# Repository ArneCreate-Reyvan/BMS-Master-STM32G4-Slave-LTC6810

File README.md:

# Master-Slave Battery Management System
### STM32G4 Master Controller · LTC6810 Slave Monitoring

A distributed Battery Management System (BMS) designed for a **102S2P electric vehicle battery pack**, featuring an STM32G4-based master controller and LTC6810-based slave monitoring units.

The system implements a modular master-slave architecture with **isoSPI daisy-chain communication**, enabling distributed battery cell voltage monitoring, temperature monitoring, centralized fault detection, and telemetry.

---

## Table of Contents

- [Overview](#overview)
- [Battery Pack Configuration](#battery-pack-configuration)
- [System Architecture](#system-architecture)
- [Monitoring Capabilities](#monitoring-capabilities)
- [Hardware Design](#hardware-design)
  - [Master BMS](#1-master-bms--stm32g4)
  - [Slave BMS](#2-slave-bms--ltc6810)
- [Communication Architecture](#communication-architecture)
- [Repository Structure](#repository-structure)
- [Development Tools](#development-tools)
- [Project Status](#project-status)
- [Future Improvements](#future-improvements)
- [Disclaimer](#disclaimer)

---

## Overview

The Battery Management System is responsible for monitoring and managing battery operating conditions to support safe and reliable electric vehicle operation.

This project implements a distributed monitoring architecture consisting of two primary subsystems:

- **Master BMS:** An STM32G4-based controller responsible for centralized system supervision, data acquisition, fault detection, and telemetry management.
- **Slave BMS:** LTC6810-based monitoring units responsible for individual battery module voltage and temperature monitoring.

The architecture separates module-level battery monitoring from high-level system management, allowing the battery pack to be monitored through interconnected slave units coordinated by a central master controller.

The hardware and PCB designs were developed using KiCad, with dedicated circuits for master control, battery monitoring, and inter-board communication.

## Battery Pack Configuration

The BMS is designed to support a **102S2P battery pack**, organized into 17 battery modules connected in series.

Each module consists of 6 series-connected cell groups, with each group containing 2 cells connected in parallel (6S2P per module).

This configuration results in 102 series-connected cell groups across the complete battery pack.

| Parameter | Specification |
|---|---|
| Battery Configuration | 102S2P |
| Total Battery Modules | 17 |
| Configuration per Module | 6S2P |
| Series Voltage Taps per Module | 6 |
| Temperature Sensors per Module | Up to 4 NTC thermistors |
| Total Voltage Monitoring Points | 102 |
| Maximum Temperature Monitoring Points | 68 |

### Battery Monitoring Distribution

Each module is equipped with local monitoring capabilities:

| Monitoring Parameter | Per Module | Entire Battery Pack |
|---|---:|---:|
| Cell Group Voltage | 6 channels | 102 channels |
| NTC Temperature | Up to 4 channels | Up to 68 channels |

This modular configuration enables the system to collect battery operating data across all 17 modules while maintaining centralized supervision.

### Main Subsystems

| Subsystem | Main Component | Responsibility |
|---|---|---|
| Master Controller | STM32G4 | Centralized control and system supervision |
| Slave Monitoring | LTC6810 | Battery cell voltage and temperature monitoring |
| Inter-board Communication | isoSPI | Isolated serial communication through a daisy-chain topology |
| Temperature Sensing | NTC Thermistors | Battery module temperature measurement |
| Data Management | STM32G4 | Monitoring data processing and telemetry |
| Fault Management | STM32G4 | Centralized fault detection and system response |

## Monitoring Capabilities

### 1. Cell Voltage Monitoring

Each slave monitoring unit uses the LTC6810 battery monitoring IC to measure six series-connected cell-group voltages within its respective battery module.

Features:
- Individual cell-group voltage measurement.
- Monitoring of all 102 series-connected cell groups.
- Distributed voltage acquisition across 17 battery modules.
- Centralized monitoring data collection.

### 2. Temperature Monitoring

Each battery module supports up to four NTC thermistors for temperature measurement.

Features:
- Up to four temperature sensing channels per module.
- Maximum of 68 temperature monitoring points across the battery pack.
- Temperature data acquisition through the slave monitoring units.
- Centralized temperature monitoring and fault evaluation.

### 3. Fault Detection

The master controller processes monitoring data received from the slave units to evaluate battery operating conditions.

The architecture supports centralized evaluation of voltage and temperature measurements to identify abnormal battery conditions.

### 4. Telemetry

The master controller manages battery monitoring data and provides a centralized interface for system-level telemetry.

Monitoring information can be collected and processed for external system integration and battery status visualization.

## Hardware Design

The hardware consists of two primary PCB designs: the Master BMS and Slave BMS.

All schematics and PCB layouts were developed using KiCad.

---

### 1. Master BMS | STM32G4

<summary>Master BMS hardware overview</summary>

**Main Controller:** STM32G4

**Primary Responsibilities:**
- Centralized BMS control and supervision.
- Communication with LTC6810 slave monitoring units.
- Monitoring data acquisition and processing.
- Battery voltage and temperature data management.
- Fault detection and system-level monitoring.
- Telemetry management.

#### Schematic

#### PCB Layout

#### PCB 3D View

---

### 2. Slave BMS | LTC6810

<summary>Slave BMS hardware overview</summary>

**Battery Monitoring IC:** LTC6810

**Primary Responsibilities:**
- Monitoring six series-connected cell-group voltages per module.
- Acquiring temperature measurements from up to four NTC thermistors per module.
- Communicating monitoring data through the isoSPI interface.
- Supporting distributed battery monitoring across 17 modules.

#### Schematic

#### PCB Layout

#### PCB 3D View

---

## Communication Architecture

The system uses **isoSPI communication** to establish communication between the STM32G4 master controller and the LTC6810 slave monitoring ICs.

The LTC6810 devices are interconnected through an **isoSPI daisy-chain topology**, allowing monitoring data to be transferred across multiple slave units through a serial communication chain.

### Communication Structure

- **Master Interface:** STM32G4 communicates with the first LTC6810 through an SPI-to-isoSPI interface.
- **Slave Communication:** LTC6810 devices communicate through their isoSPI interfaces.
- **Topology:** Daisy-chain configuration connecting the monitoring ICs.
- **Data Acquisition:** The master controller coordinates communication and collects battery monitoring information from the slave units.

### Communication Advantages

- Differential communication over twisted-pair connections.
- Galvanically isolated communication between battery monitoring circuits and the master interface when implemented with the appropriate isolation coupling components.
- Reduced wiring complexity compared with individual communication connections to every monitoring unit.
- Scalable communication architecture for distributed battery monitoring.

## Development Tools

| Tool / Component | Purpose |
|---|---|
| KiCad | Schematic capture and PCB design |
| STM32G4 | Master microcontroller |
| LTC6810 | Battery cell monitoring IC |
| isoSPI | Isolated serial communication interface |
| NTC Thermistors | Temperature sensing |
| Embedded C/C++ | Firmware development |

## Project Status

The hardware and firmware development have been completed, with further refinement and validation remaining.

| Development Area | Status |
|---|---|
| System Architecture | Completed |
| Master BMS Hardware | Completed |
| Slave BMS Hardware | Completed |
| PCB Design | Completed |
| Master Firmware | Developed |
| Slave Firmware | Developed |
| Communication Implementation | Developed |
| Documentation | Ongoing |
| Design Refinement & Validation | Ongoing |

## Future Improvements

- Further refinement of schematic and PCB designs.
- Additional communication reliability testing.
- Expanded battery fault detection and protection mechanisms.
- Improved telemetry and monitoring capabilities.
- Further validation of voltage and temperature measurement accuracy.
- System-level integration and testing.

## Disclaimer

This project is an engineering development project intended for educational and electric vehicle research purposes.

The documented design should not be considered a production-ready battery protection system without appropriate electrical, functional, and safety validation.

High-voltage battery systems require proper insulation, isolation, protection mechanisms, and qualified engineering supervision before physical implementation.

---

**Developed for electric vehicle battery management and high-voltage electrical system applications.**

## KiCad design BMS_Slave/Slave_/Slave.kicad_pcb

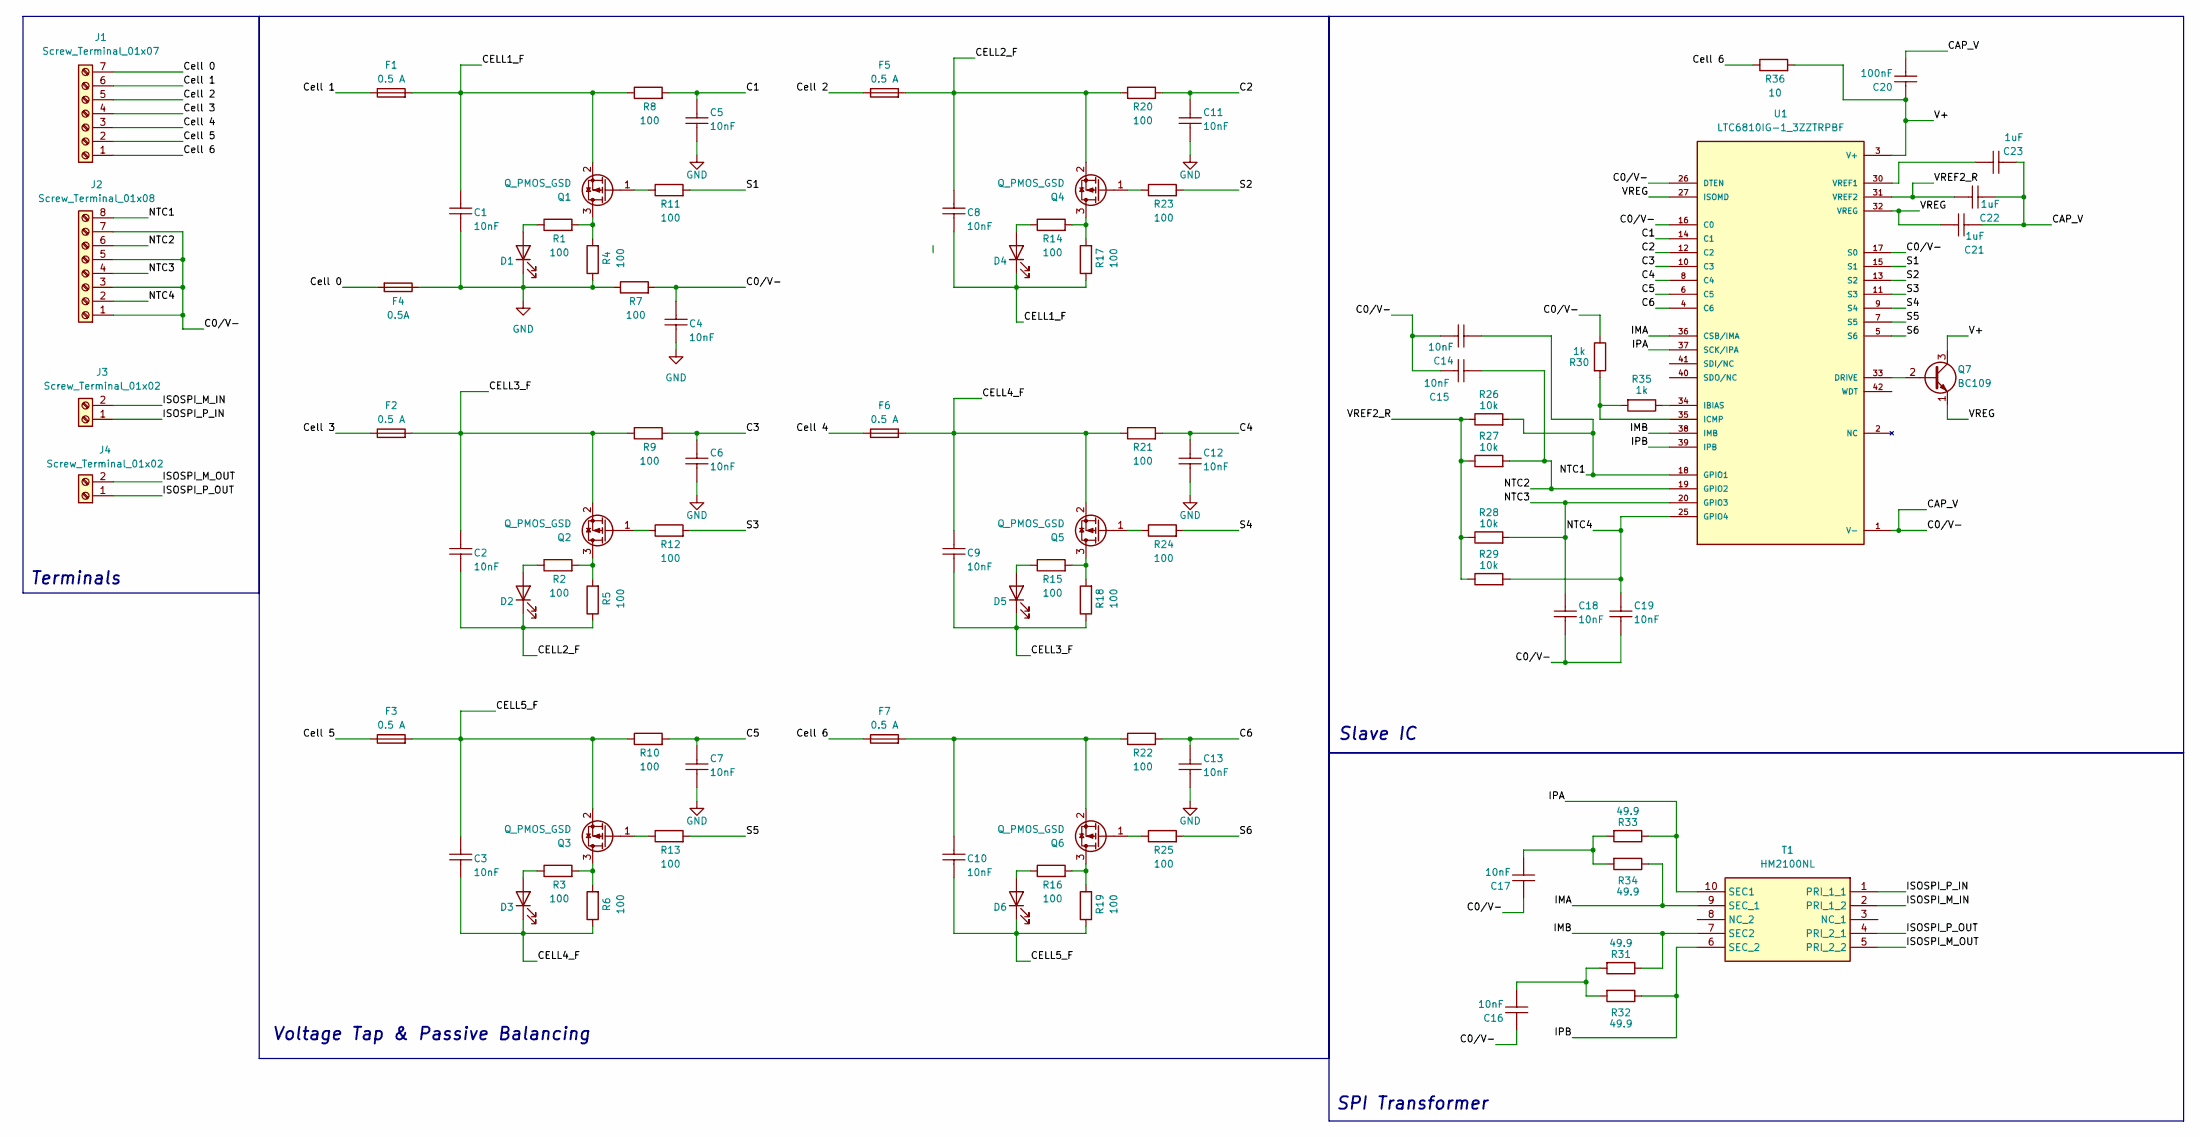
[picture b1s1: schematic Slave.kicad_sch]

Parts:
C1, C2, C3, C4, C5, C6, C7, C8, C9, C10, C11, C12, C13, C14, C15, C16, C17, C18, C19: 10nF; C_0603_1608Metric
C20: 100nF; C_0603_1608Metric
C21, C22, C23: 1uF; C_0603_1608Metric
D1, D2, D3, D4, D5, D6: LED; LED_0603_1608Metric
F1, F2, F3, F5, F6, F7: 0.5 A; Fuse_1206_3216Metric
F4: 0.5A; Fuse_1206_3216Metric
J1: Screw_Terminal_01x07; TerminalBlock_Phoenix_MKDS-1,5-7-5.08_1x07_P5.08mm_Horizont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
J2: Screw_Terminal_01x08; TerminalBlock_Phoenix_MKDS-1,5-8-5.08_1x08_P5.08mm_Horizont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
J3, J4: Screw_Terminal_01x02; TerminalBlock_Phoenix_MKDS-1,5-2-5.08_1x02_P5.08mm_Horizont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
Q1, Q2, Q3, Q4, Q5, Q6: Q_PMOS_GSD; SOT-23
Q7: BC109; TO-18-3
R1, R2, R3, R4, R5, R6, R7, R8, R9, R10, R11, R12, R13, R14, R15, R16, R17, R18, R19, R20, R21, R22, R23, R24, R25: 100; R_0805_2012Metric
R26, R27, R28, R29: 10k; R_0201_0603Metric
R30, R35: 1k; R_0201_0603Metric
R31, R32, R33, R34: 49.9; R_0201_0603Metric
R36: 10; R_0201_0603Metric
T1: HM2100NL; SOP254P1493X345-10N; Mouser Part Number 673-HM2100NL
U1: LTC6810IG-1_3ZZTRPBF; 05-08-1754_ADI-L; MPN LTC6810IG-1#3ZZTRPBF

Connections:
/C1: C5.1, R8.2, U1.14 (C1)
/C2: C11.1, R20.2, U1.12 (C2)
/C3: C6.1, R9.2, U1.10 (C3)
/C4: C12.1, R21.2, U1.8 (C4)
/C5: C7.1, R10.2, U1.6 (C5)
/C6: C13.1, R22.2, U1.4 (C6)
/CELL1_F: C1.1, C8.2, D4.1 (K), F1.2, Q1.2 (S), R8.1, R17.1
/CELL2_F: C2.2, C8.1, D2.1 (K), F5.2, Q4.2 (S), R5.1, R20.1
/CELL3_F: C2.1, C9.2, D5.1 (K), F2.2, Q2.2 (S), R9.1, R18.1
/CELL4_F: C3.2, C9.1, D3.1 (K), F6.2, Q5.2 (S), R6.1, R21.1
/CELL5_F: C3.1, C10.2, D6.1 (K), F3.2, Q3.2 (S), R10.1, R19.1
/Cell 0: F4.2, J1.7
/Cell 1: F1.1, J1.6
/Cell 2: F5.1, J1.5
/Cell 3: F2.1, J1.4
/Cell 4: F6.1, J1.3
/Cell 5: F3.1, J1.2
/Cell 6: F7.1, J1.1, R36.1
/IMA: R34.1, T1.9 (SEC_1), U1.36 (CSB/IMA)
/IMB: R31.1, T1.7 (SEC2), U1.38 (IMB)
/IPA: R33.1, T1.10 (SEC1), U1.37 (SCK/IPA)
/IPB: R32.1, T1.6 (SEC_2), U1.39 (IPB)
/ISOSPI_M_IN: J3.2, T1.2 (PRI_1_2)
/ISOSPI_M_OUT: J4.2, T1.5 (PRI_2_2)
/ISOSPI_P_IN: J3.1, T1.1 (PRI_1_1)
/ISOSPI_P_OUT: J4.1, T1.4 (PRI_2_1)
/NTC1: C14.1, J2.8, R26.2, U1.18 (GPIO1)
/NTC2: C15.1, J2.6, R27.2, U1.19 (GPIO2)
/NTC3: C18.1, J2.4, R28.2, U1.20 (GPIO3)
/NTC4: C19.1, J2.2, R29.2, U1.25 (GPIO4)
/S1: R11.2, U1.15 (S1)
/S2: R23.2, U1.13 (S2)
/S3: R12.2, U1.11 (S3)
/S4: R24.2, U1.9 (S4)
/S5: R13.2, U1.7 (S5)
/S6: R25.2, U1.5 (S6)
/V+: C20.1, Q7.3 (C), R36.2, U1.3 (V+)
/VREF2_R: C22.1, R26.1, R27.1, R28.1, R29.1, U1.31 (VREF2)
/VREG: C21.1, Q7.1 (E), U1.27 (ISOMD), U1.32 (VREG)
GND: C1.2, C4.2, C5.2, C6.2, C7.2, C11.2, C12.2, C13.2, D1.1 (K), F4.1, R4.1, R7.1
unnamed: C16.2, R31.2, R32.2
unnamed: C17.2, R33.2, R34.2
unnamed: D1.2 (A), R1.1
unnamed: D2.2 (A), R2.1
unnamed: D3.2 (A), R3.1
unnamed: D4.2 (A), R14.1
unnamed: D5.2 (A), R15.1
unnamed: D6.2 (A), R16.1
unnamed: Q1.3 (D), R1.2, R4.2
unnamed: Q1.1 (G), R11.1
unnamed: Q2.3 (D), R2.2, R5.2
unnamed: Q2.1 (G), R12.1
unnamed: Q3.3 (D), R3.2, R6.2
unnamed: Q3.1 (G), R13.1
unnamed: Q4.3 (D), R14.2, R17.2
unnamed: Q4.1 (G), R23.1
unnamed: Q5.3 (D), R15.2, R18.2
unnamed: Q5.1 (G), R24.1
unnamed: Q6.3 (D), R16.2, R19.2
unnamed: Q6.1 (G), R25.1
unnamed: C10.1, F7.2, Q6.2 (S), R22.1
unnamed: Q7.2 (B), U1.33 (DRIVE)
unnamed: R35.1, U1.34 (IBIAS)
unnamed: R30.2, R35.2, U1.35 (ICMP)
unnamed: C23.1, U1.30 (VREF1)
V-: C4.1, C14.2, C15.2, C16.1, C17.1, C18.2, C19.2, C20.2, C21.2, C22.2, C23.2, J2.1, J2.3, J2.5, J2.7, R7.2, R30.1, U1.1 (V-), U1.16 (C0), U1.17 (S0), U1.21 (V-), U1.22 (V-), U1.23 (V-), U1.24 (V-), U1.26 (DTEN), U1.28 (V-), U1.29 (V-), U1.43 (V-), U1.44 (V-)

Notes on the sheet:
SPI Transformer
Terminals
Slave IC
Voltage Tap & Passive Balancing

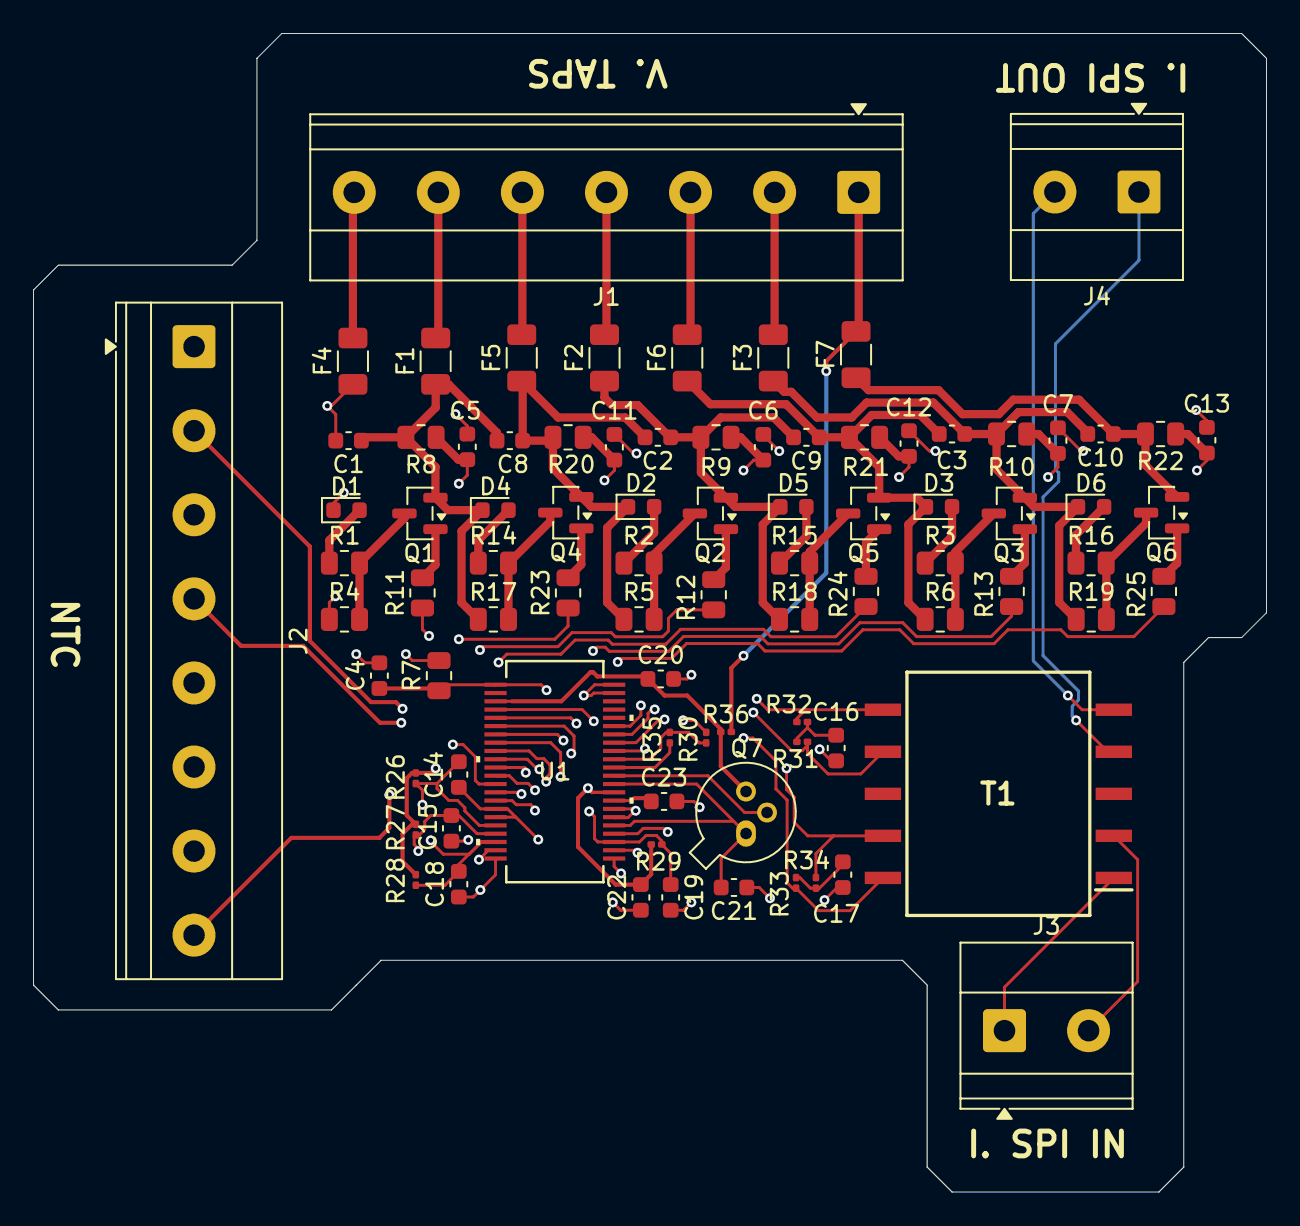
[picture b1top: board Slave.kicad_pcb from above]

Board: 4 copper layers, 74.5 x 70.0 mm, 85 parts (0 on the bottom side), 66 nets.

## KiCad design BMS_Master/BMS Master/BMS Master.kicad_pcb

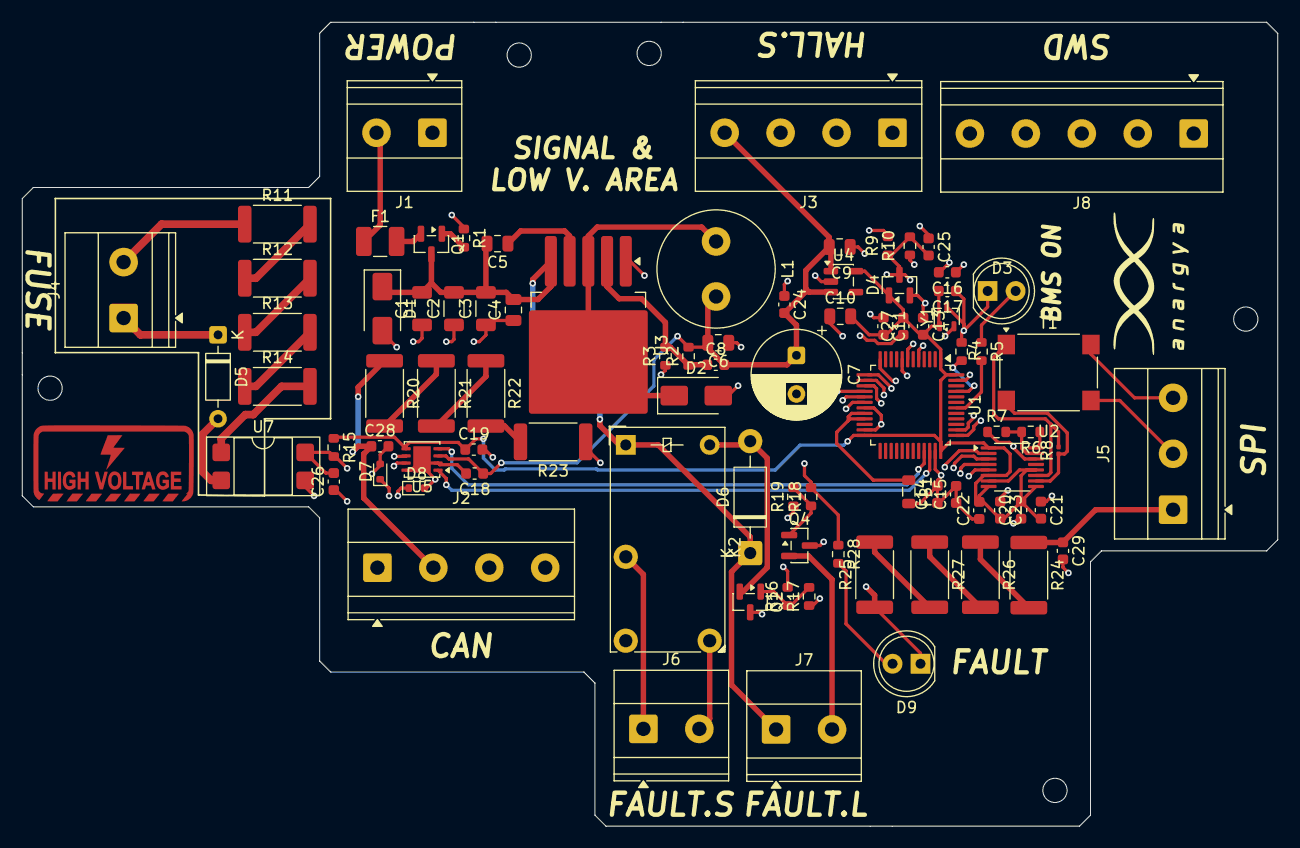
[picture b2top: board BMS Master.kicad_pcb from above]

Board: 4 copper layers, 114.0 x 73.0 mm, 88 parts (0 on the bottom side), 59 nets.

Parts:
C1, C2: 10uF; C_1206_3216Metric
C3: 220uF; C_1206_3216Metric
C4, C5, C6: 1uF; C_0805_2012Metric
C7: 330uF; CP_Radial_D8.0mm_P3.50mm
C8: 33nF; C_0603_1608Metric
C9, C10: 10uF; C_0805_2012Metric
C11, C13, C15, C16, C17, C18, C19, C20, C22, C24, C25, C26, C27, C28, C29: 100nF; C_0603_1608Metric
C14, C21, C23: 1uF; C_0603_1608Metric
D1: SMAJ24A; D_SMA
D2: D_Schottky; D_SMA
D3, D9: LED; LED_D5.0mm
D4: BAT54S; SOT-23
D5: 1N4148; D_DO-35_SOD27_P7.62mm_Horizontal
D6: 1N4007; D_DO-41_SOD81_P10.16mm_Horizontal
D7, D8: ESD5Zxx; D_SOD-523
F1: Fuse; Fuse_1210_3225Metric_Pad1.42x2.65mm_HandSolder
FB1: FerriteBead; L_0805_2012Metric
J1, J4, J6, J7: Screw_Terminal_01x02; TerminalBlock_Phoenix_MKDS-1,5-2-5.08_1x02_P5.08mm_Horizont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
J2, J3: Screw_Terminal_01x04; TerminalBlock_Phoenix_MKDS-1,5-4-5.08_1x04_P5.08mm_Horizont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
J5: Screw_Terminal_01x03; TerminalBlock_Phoenix_MKDS-1,5-3-5.08_1x03_P5.08mm_Horizont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
J8: Screw_Terminal_01x05; TerminalBlock_Phoenix_MKDS-1,5-5-5.08_1x05_P5.08mm_Horizont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
K2: FINDER-32.21-x000; Relay_SPDT_Finder_32.21-x000
L1: 47uH; L_Radial_D10.5mm_P5.00mm_Abacron_AISR-01
Q1: NTR2101P; SOT-23
Q2, Q4: 2N7002; SOT-23
R1, R2, R3, R4, R9, R10, R15: 10k; R_0603_1608Metric
R5, R16, R18, R28: 1k; R_0603_1608Metric
R6: 1.21k; R_0603_1608Metric
R7: 787; R_0603_1608Metric
R8: 100; R_0201_0603Metric
R11, R12, R13, R14: 75k; R_2512_6332Metric
R17, R19: 100k; R_0603_1608Metric
R20, R21, R22, R23, R24, R25, R26, R27: 250k; R_2512_6332Metric
T1: PE-68386NL; Pulse_PA2001NL
U1: STM32G473CBTx; LQFP-48_7x7mm_P0.5mm
U2: LTC6820; MSOP-16_3x4.039mm_P0.5mm
U3: XL4015; TO-263-5_TabPin3
U4: AP2112K-3.3; SOT-23-5
U5: TJA1051TK-3; HVSON-8-1EP_3x3mm_P0.65mm_EP1.6x2.4mm
U7: Optocoupler_DC_PhotoNPN_AKEC; DIP-4_W7.62mm_SMDSocket_SmallPads
Y1: MAX7375AXR805; SOT-323_SC-70

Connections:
/12V_LV: F1.1, J1.2
/12V_SW: C1.2, C2.2, C3.2, C4.2, C5.2, D1.1 (A1), D6.1 (K), J7.1, K2.A1, Q1.3 (D), U3.5 (VIN)
/+5V: C6.2, C7.1, C8.2, C9.2, C18.1, C24.2, J3.4, L1.2, R2.2, U4.1 (VIN), U4.3 (EN), U5.3 (VCC)
/CAN_H: D8.1 (K), J2.4, U5.7 (CANH)
/CAN_L: D7.1 (K), J2.3, U5.6 (CANL)
/COM: J6.2, K2.12
/FAULT_LED: R18.2, R28.1, U1.18 (PB2)
/FAULT_SIG: R16.2, U1.17 (PB1)
/FUSE_A: J4.2, R11.1
/FUSE_B: D5.1 (K), J4.1
/GPIO_12: U1.12 (PA4), U2.5 (CS#)
/HALL_OUT: J3.3, R9.2
/HALL_VOLT: C25.2, D4.3 (COM), R9.1, R10.2, U1.8 (PA0)
/ISOSPI_M: J5.2, T1.4
/ISOSPI_P: J5.3, T1.6
/LAMP_SINK: J7.2, Q4.2 (S)
/LDO_OUT_3V3: C10.2, C11.2, C13.2, C17.2, C19.1, C20.2, C21.2, C22.2, C23.2, C27.2, D4.1 (A), R15.1, U1.1 (VBAT), U1.24 (VDD), U1.36 (VDD), U1.48 (VDD), U2.1 (EN), U2.6 (VDDS), U2.7 (POL), U2.8 (PHA), U2.9 (VDD), U2.12 (MSTR), U4.5 (VOUT), U5.5 (VIO), Y1.1 (V+)
/NO: J6.1, K2.11
/NRST: C16.2, J8.4, U1.7 (PG10)
/OPTO_COL: C26.2, R15.2, U1.16 (PB0), U7.4
/PRIM_1: R8.2, T1.1, U2.11 (IP)
/PRIM_2: R8.1, T1.3, U2.10 (IM)
/RXD: U1.33 (PA11), U5.4 (RXD)
/SHIELD_CAN: C28.1, J2.2, R20.1
/SHIELD_SPI: C29.1, J5.1, R24.1
/SPI1_MISO: U1.14 (PA6), U2.3 (MISO)
/SPI1_MOSI: U1.15 (PA7), U2.2 (MOSI)
/SPI1_SCK: U1.13 (PA5), U2.4 (SCK)
/SWCLK: J8.3, U1.38 (PA14)
/SWDIO: J8.2, U1.37 (PA13)
/TXD: U1.34 (PA12), U5.1 (TXD)
/VDDA: FB1.1, U1.20 (VREF+), U1.21 (VDDA)
GND: C1.1, C2.1, C3.1, C4.1, C6.1, C7.2, C9.1, C10.1, C11.1, C13.1, C14.1, C14.2, C15.1, C15.2, C16.1, C17.1, C18.2, C19.2, C20.1, C21.1, C22.1, C23.1, C24.1, C25.1, C26.1, C27.1, C28.2, C29.2, D1.2 (A2), D2.2 (A), D3.1 (K), D4.2 (K), D7.2 (A), D8.2 (A), D9.1 (K), FB1.2, J1.1, J2.1, J3.1, J8.1, Q2.3 (D), Q4.3 (D), R1.1, R3.1, R4.1, R7.1, R10.1, R17.1, R19.1, R23.1, R25.1, U1.19 (VSSA), U1.23 (VSS), U1.35 (VSS), U1.47 (VSS), U2.14 (GND), U3.1 (GND), U4.2 (GND), U5.2 (GND), U5.8 (S), U5.9 (GND), U7.3, Y1.3 (GND)
unnamed: D2.1 (K), L1.1, U3.3 (SW)
unnamed: D3.2 (A), R5.1
unnamed: D5.2 (A), U7.2
unnamed: D6.2 (A), K2.A2, Q2.2 (S)
unnamed: D9.2 (A), R28.2
unnamed: Q1.1 (G), R1.2
unnamed: F1.2, Q1.2 (S)
unnamed: Q2.1 (G), R16.1, R17.2
unnamed: Q4.1 (G), R18.1, R19.2
unnamed: R11.2, R12.1
unnamed: R12.2, R13.1
unnamed: R13.2, R14.1
unnamed: R14.2, U7.1
unnamed: R20.2, R21.1
unnamed: R21.2, R22.1
unnamed: R22.2, R23.2
unnamed: R24.2, R26.1
unnamed: R25.2, R27.2
unnamed: R26.2, R27.1
unnamed: R5.2, U1.42 (PB5)
unnamed: R4.2, U1.45 (PB8)
unnamed: U1.5 (PF0), Y1.2 (CLOCK)
unnamed: R6.1, U2.16 (IBIAS)
unnamed: R6.2, R7.2, U2.15 (ICMP)
unnamed: C8.1, R2.1, R3.2, U3.2 (FB)
unnamed: C5.1, U3.4 (VC)
